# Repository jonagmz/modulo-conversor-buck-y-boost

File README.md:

# modulo elevador y reductor de voltaje 

Voltaje de entrada: 5V (micro USB)

Voltajes de salida: 12V y 3.3V

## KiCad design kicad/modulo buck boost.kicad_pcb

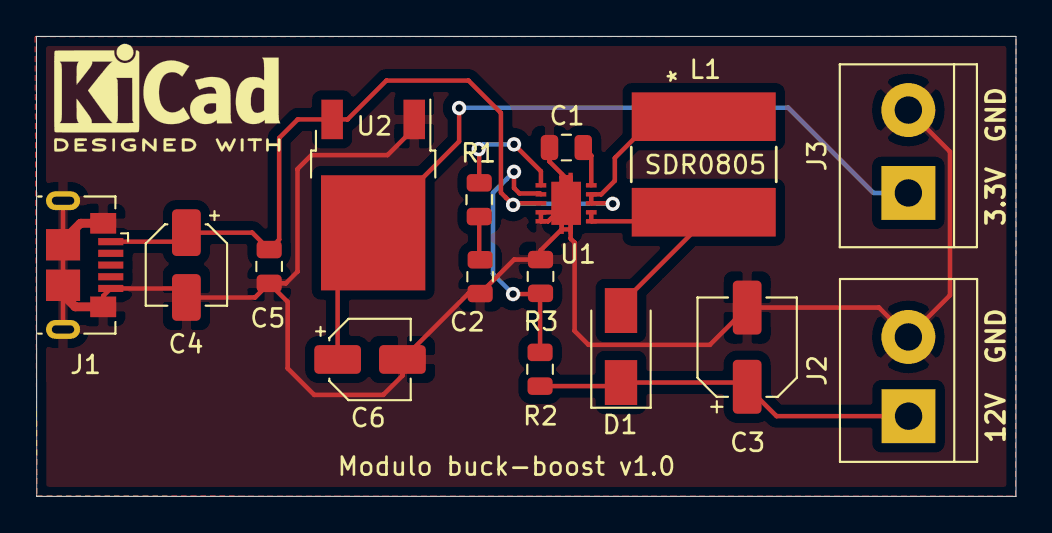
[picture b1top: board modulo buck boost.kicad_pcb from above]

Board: 2 copper layers, 54.4 x 25.6 mm, 16 parts (0 on the bottom side), 9 nets.

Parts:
C1: 100nF; C_0805_2012Metric
C2: 820pF; C_0805_2012Metric
C3: 22uF; CP_Elec_5x4.5
C4, C6: 10uF; CP_Elec_4x4.5
C5: 1uF; C_0805_2012Metric
D1: B340; D_SMA
J1: USB_B_Micro; USB_Micro-B_GCT_USB3076-30-A
J2, J3: Conn_01x02_Male; TerminalBlock_bornier-2_P5.08mm
L1: SDR0805; SDR0805-220ML
R1: 105K; R_0805_2012Metric
R2: 232K; R_0805_2012Metric
R3: 26.7K; R_0805_2012Metric
U1: TPS61087DSCR; TPS61087-02
U2: LM1117-3.3; TO-252-2

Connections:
+3V3: C6.1, J3.1, U2.2
+5V: C4.1, C5.1, J1.1, L1.1, U1.3, U1.8, U1.9, U2.3
+12V: C3.1, D1.1, J2.1, R2.2
/FB: R2.1, R3.1, U1.2
/SW: D1.2, L1.2, U1.6, U1.7
GND: C1.2, C2.2, C3.2, C4.2, C5.2, C6.2, J1.5, J1.6, J2.2, J3.2, R3.2, U1.4, U1.5, U1.11, U2.1
unnamed: C1.1, U1.10
unnamed: C2.1, R1.2
unnamed: R1.1, U1.1

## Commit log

2019-06-18 iniciando proyecto
2019-06-18 esquematico actualizado
2019-06-20 se realizo las conexiones en el esquematico
2019-06-22 actualizaciones
2019-06-23 se agrego un archivo
2019-08-10 placa v1
2019-08-23 Actualizacion

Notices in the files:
parts and their libraries:
Copyright 2016 Accelerated Designs. All rights reserved.
